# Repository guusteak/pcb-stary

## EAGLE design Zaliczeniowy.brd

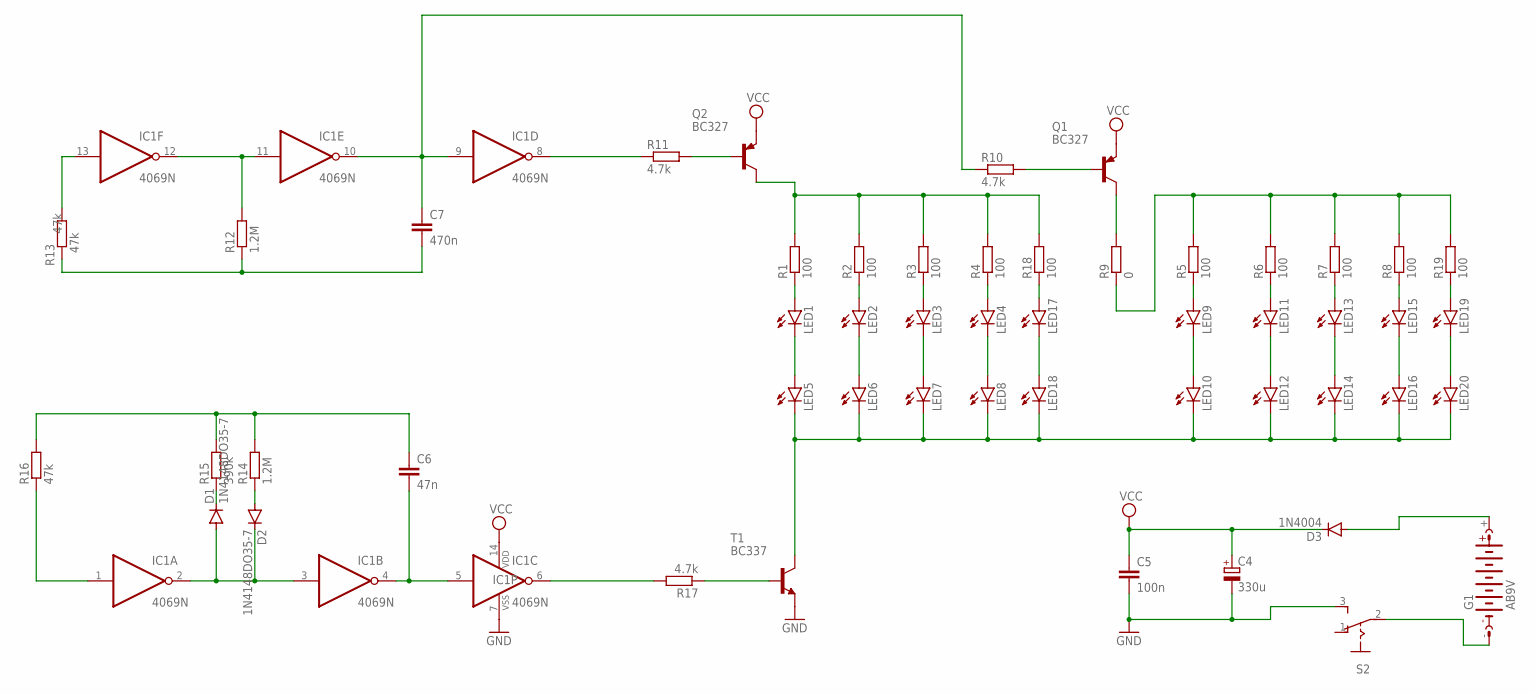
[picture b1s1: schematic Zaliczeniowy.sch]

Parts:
C4: 330u; E2-5
C5: 100n; C025-024X044
C6: 47n; C025-024X044
C7: 470n; C025-024X044
D1, D2: 1N4148DO35-7; DO35-7
D3: 1N4004; DO41-10
G1: AB9V
IC1: 4069N; DIL14
LED1, LED2, LED3, LED4, LED5, LED6, LED7, LED8, LED9, LED10, LED11, LED12, LED13, LED14, LED15, LED16, LED17, LED18, LED19, LED20: LED5MM
Q1, Q2: BC327; TO92
R1, R2, R3, R4, R5, R6, R7, R8, R18, R19: 100; 0207/7
R9: 0; 0207/7
R10, R11, R17: 4.7k; 0207/7
R12, R14: 1.2M; 0207/7
R13, R16: 47k; 0207/7
R15: 390k; 0207/7
S2: 255SB
T1: BC337; TO92-CBE

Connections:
+VCC: D3.A, G1.+
GND: C4.-, C5.2, IC1.7 (VSS), S2.3 (S), T1.E
unnamed: LED1.A, R1.1
unnamed: LED2.A, R2.1
unnamed: LED3.A, R3.1
unnamed: LED4.A, R4.1
unnamed: LED1.K (C), LED5.A
unnamed: LED2.K (C), LED6.A
unnamed: LED3.K (C), LED7.A
unnamed: LED17.A, R18.1
unnamed: Q2.3 (C), R1.2, R2.2, R3.2, R4.2, R18.2
unnamed: LED5.K (C), LED6.K (C), LED7.K (C), LED8.K (C), LED10.K (C), LED12.K (C), LED14.K (C), LED16.K (C), LED18.K (C), LED20.K (C), T1.C
unnamed: LED9.K (C), LED10.A
unnamed: LED11.K (C), LED12.A
unnamed: LED13.K (C), LED14.A
unnamed: LED15.K (C), LED16.A
unnamed: LED15.A, R8.1
unnamed: LED13.A, R7.1
unnamed: LED11.A, R6.1
unnamed: LED9.A, R5.1
unnamed: R5.2, R6.2, R7.2, R8.2, R9.1, R19.2
unnamed: IC1.13 (I), R13.2
unnamed: Q1.3 (C), R9.2
unnamed: Q1.2 (B), R10.2
unnamed: IC1.11 (I), IC1.12 (O), R12.2
unnamed: IC1.1 (I), R16.1
unnamed: C7.1, IC1.9 (I), IC1.10 (O), R10.1
unnamed: Q2.2 (B), R11.2
unnamed: IC1.8 (O), R11.1
unnamed: C7.2, R12.1, R13.1
unnamed: D1.C, R15.1
unnamed: D2.A, R14.1
unnamed: D1.A, D2.C, IC1.2 (O), IC1.3 (I)
unnamed: C6.1, R14.2, R15.2, R16.2
unnamed: C6.2, IC1.4 (O), IC1.5 (I)
unnamed: IC1.6 (O), R17.2
unnamed: R17.1, T1.B
unnamed: G1.-, S2.2
unnamed: LED4.K (C), LED8.A
unnamed: LED17.K (C), LED18.A
unnamed: LED19.A, R19.1
unnamed: LED19.K (C), LED20.A
VCC: C4.+, C5.1, D3.C, IC1.14 (VDD), Q1.1 (E), Q2.1 (E)

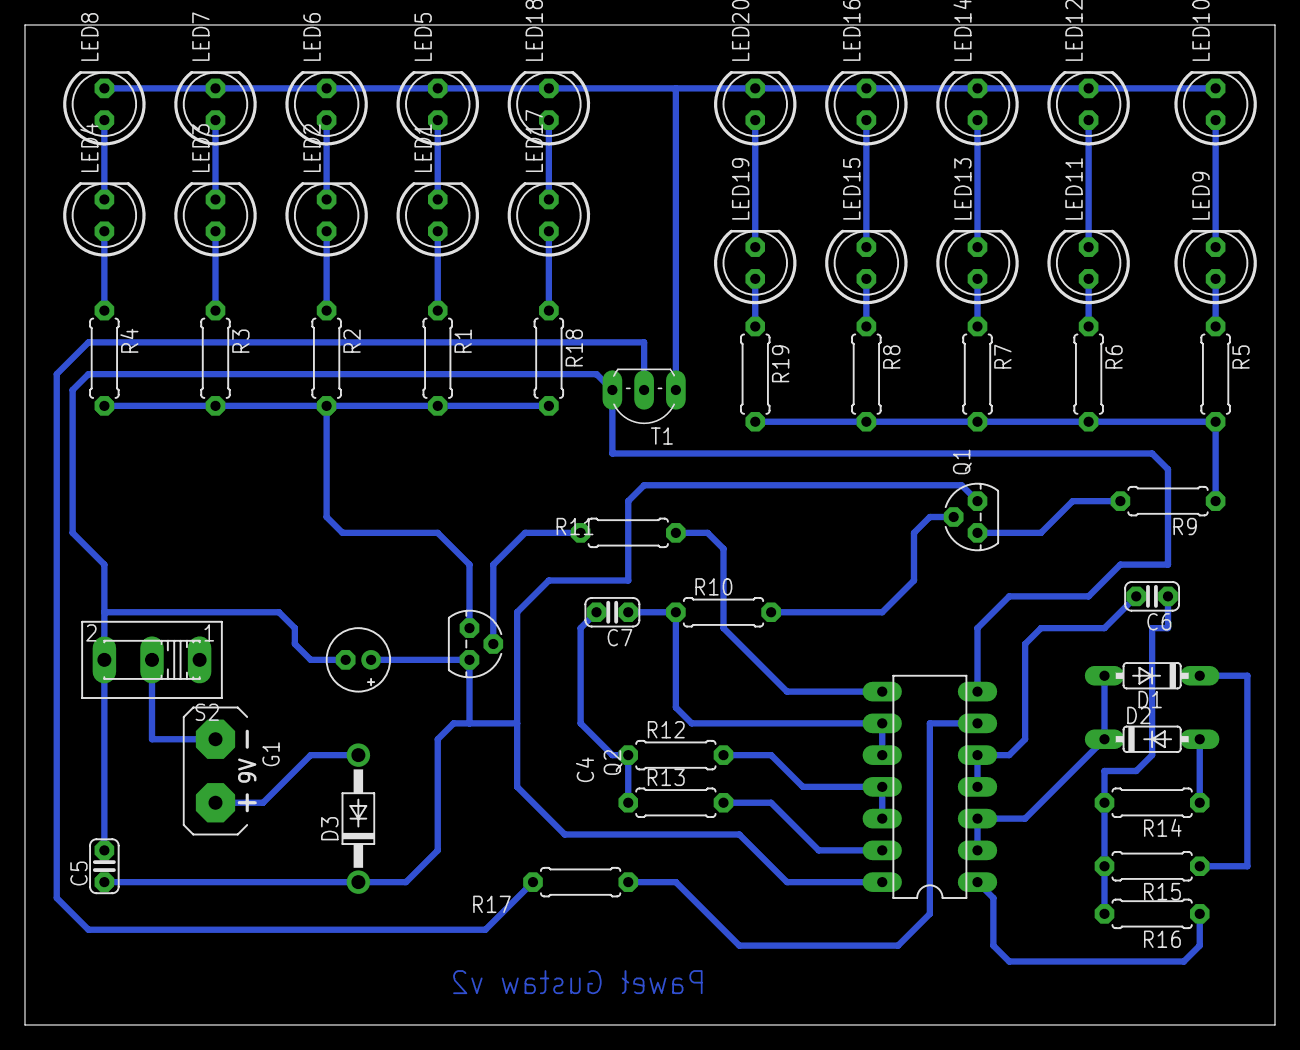
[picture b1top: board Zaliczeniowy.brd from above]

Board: 2 copper layers, 100.0 x 80.0 mm, 52 parts (0 on the bottom side), 43 nets.

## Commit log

2023-02-06 it is what it is
